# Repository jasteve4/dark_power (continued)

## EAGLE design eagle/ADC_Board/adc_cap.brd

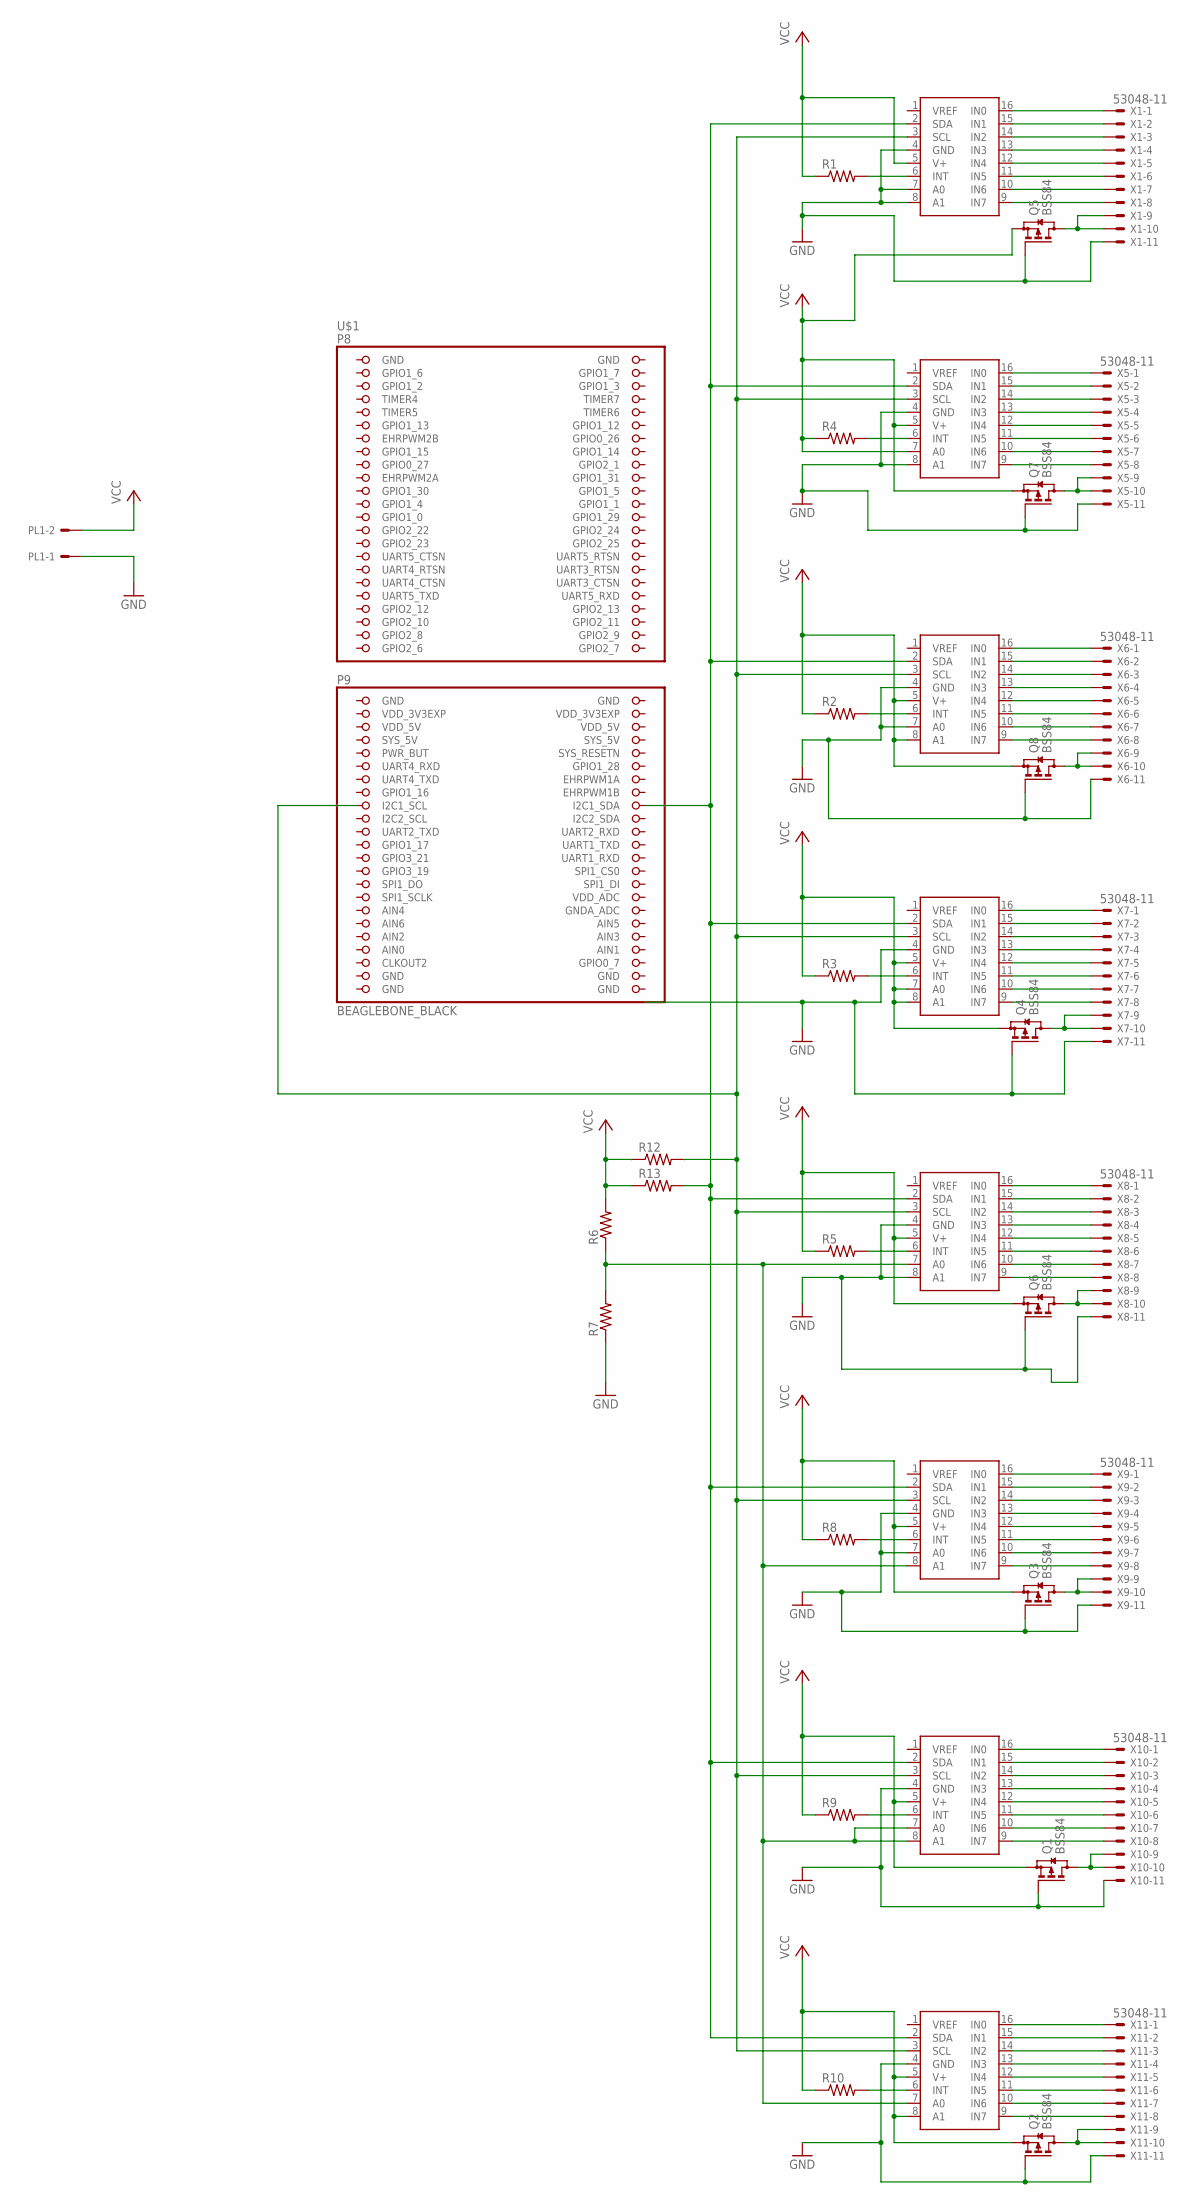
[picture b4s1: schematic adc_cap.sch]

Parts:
PL1: 555X-2H; 5569-2
Q1, Q2, Q3, Q4, Q5, Q6, Q7, Q8: BSS84; SOT23
R1, R2, R3, R4, R5, R6, R7, R8, R9, R10, R12, R13: R-US_R0805; R0805
U$1: BEAGLEBONE_BLACK; BEAGEBONE
U$2, U$3, U$4, U$5, U$6, U$7, U$8, U$9: ADC128D818; ADC12_SD
X1, X5, X6, X7, X8, X9, X10, X11: 53048-11

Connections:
AIN0: U$1.146 (AIN0)
GND: PL1.1, Q1.1 (G), Q2.1 (G), Q3.1 (G), Q4.1 (G), Q5.1 (G), Q6.1 (G), Q7.1 (G), Q8.1 (G), R7.1, U$1.137 (GND), U$1.138 (GND), U$1.139 (GND), U$1.140 (GND), U$1.141 (GND), U$1.142 (GND), U$1.183 (GND), U$1.184 (GND), U$2.4 (GND), U$2.8 (A1), U$3.4 (GND), U$3.7 (A0), U$3.8 (A1), U$4.4 (GND), U$4.7 (A0), U$5.4 (GND), U$6.4 (GND), U$6.8 (A1), U$7.4 (GND), U$7.7 (A0), U$8.4 (GND), U$9.4 (GND), X1.11, X5.11, X6.11, X7.11, X8.11, X9.11, X10.11, X11.11
unnamed: U$3.16 (IN0), X1.1
unnamed: U$3.15 (IN1), X1.2
unnamed: U$3.14 (IN2), X1.3
unnamed: U$3.13 (IN3), X1.4
unnamed: U$3.12 (IN4), X1.5
unnamed: U$3.11 (IN5), X1.6
unnamed: U$3.10 (IN6), X1.7
unnamed: U$3.9 (IN7), X1.8
unnamed: U$9.16 (IN0), X11.1
unnamed: U$9.15 (IN1), X11.2
unnamed: U$9.14 (IN2), X11.3
unnamed: U$9.13 (IN3), X11.4
unnamed: U$9.12 (IN4), X11.5
unnamed: U$9.11 (IN5), X11.6
unnamed: U$9.10 (IN6), X11.7
unnamed: U$9.9 (IN7), X11.8
unnamed: U$8.16 (IN0), X10.1
unnamed: U$8.15 (IN1), X10.2
unnamed: R4.2, U$2.6 (INT)
unnamed: U$8.14 (IN2), X10.3
unnamed: U$8.13 (IN3), X10.4
unnamed: U$8.12 (IN4), X10.5
unnamed: U$8.11 (IN5), X10.6
unnamed: U$8.10 (IN6), X10.7
unnamed: U$8.9 (IN7), X10.8
unnamed: R2.2, U$4.6 (INT)
unnamed: U$7.16 (IN0), X9.1
unnamed: U$7.15 (IN1), X9.2
unnamed: U$7.14 (IN2), X9.3
unnamed: U$7.13 (IN3), X9.4
unnamed: U$7.12 (IN4), X9.5
unnamed: U$7.11 (IN5), X9.6
unnamed: U$7.10 (IN6), X9.7
unnamed: U$7.9 (IN7), X9.8
unnamed: R3.2, U$5.6 (INT)
unnamed: U$6.16 (IN0), X8.1
unnamed: U$6.15 (IN1), X8.2
unnamed: U$6.14 (IN2), X8.3
unnamed: U$6.13 (IN3), X8.4
unnamed: U$6.12 (IN4), X8.5
unnamed: U$6.11 (IN5), X8.6
unnamed: U$6.10 (IN6), X8.7
unnamed: U$6.9 (IN7), X8.8
unnamed: R5.2, U$6.6 (INT)
unnamed: R6.1, R7.2, U$6.7 (A0), U$7.8 (A1), U$8.7 (A0), U$8.8 (A1), U$9.7 (A0)
unnamed: U$5.16 (IN0), X7.1
unnamed: U$5.15 (IN1), X7.2
unnamed: U$5.14 (IN2), X7.3
unnamed: U$5.13 (IN3), X7.4
unnamed: U$5.12 (IN4), X7.5
unnamed: U$5.11 (IN5), X7.6
unnamed: U$5.10 (IN6), X7.7
unnamed: U$5.9 (IN7), X7.8
unnamed: R8.2, U$7.6 (INT)
unnamed: R12.2, U$1.168 (I2C1_SCL), U$2.3 (SCL), U$3.3 (SCL), U$4.3 (SCL), U$5.3 (SCL), U$6.3 (SCL), U$7.3 (SCL), U$8.3 (SCL), U$9.3 (SCL)
unnamed: U$4.16 (IN0), X6.1
unnamed: U$4.15 (IN1), X6.2
unnamed: U$4.14 (IN2), X6.3
unnamed: U$4.13 (IN3), X6.4
unnamed: U$4.12 (IN4), X6.5
unnamed: U$4.11 (IN5), X6.6
unnamed: U$4.10 (IN6), X6.7
unnamed: U$4.9 (IN7), X6.8
unnamed: R9.2, U$8.6 (INT)
unnamed: U$2.16 (IN0), X5.1
unnamed: U$2.15 (IN1), X5.2
unnamed: R1.2, U$3.6 (INT)
unnamed: U$2.14 (IN2), X5.3
unnamed: U$2.13 (IN3), X5.4
unnamed: U$2.12 (IN4), X5.5
unnamed: U$2.11 (IN5), X5.6
unnamed: U$2.10 (IN6), X5.7
unnamed: U$2.9 (IN7), X5.8
unnamed: R10.2, U$9.6 (INT)
unnamed: Q5.3 (D), X1.9, X1.10
unnamed: Q4.3 (D), X7.9, X7.10
unnamed: Q8.3 (D), X6.9, X6.10
unnamed: Q1.3 (D), X10.9, X10.10
unnamed: Q7.3 (D), X5.9, X5.10
unnamed: Q6.3 (D), X8.9, X8.10
unnamed: Q2.3 (D), X11.9, X11.10
unnamed: R13.2, U$1.165 (I2C1_SDA), U$2.2 (SDA), U$3.2 (SDA), U$4.2 (SDA), U$5.2 (SDA), U$6.2 (SDA), U$7.2 (SDA), U$8.2 (SDA), U$9.2 (SDA)
unnamed: Q3.3 (D), X9.9, X9.10
SYS_5V: U$1.178 (SYS_5V)
VCC: PL1.2, Q1.2 (S), Q2.2 (S), Q3.2 (S), Q4.2 (S), Q5.2 (S), Q6.2 (S), Q7.2 (S), Q8.2 (S), R1.1, R2.1, R3.1, R4.1, R5.1, R6.2, R8.1, R9.1, R10.1, R12.1, R13.1, U$2.5 (V+), U$2.7 (A0), U$3.5 (V+), U$4.5 (V+), U$4.8 (A1), U$5.5 (V+), U$5.7 (A0), U$5.8 (A1), U$6.5 (V+), U$7.5 (V+), U$8.5 (V+), U$9.5 (V+), U$9.8 (A1)
VDD_3V3EXP: U$1.181 (VDD_3V3EXP), U$1.182 (VDD_3V3EXP)
VDD_5V: U$1.179 (VDD_5V), U$1.180 (VDD_5V)

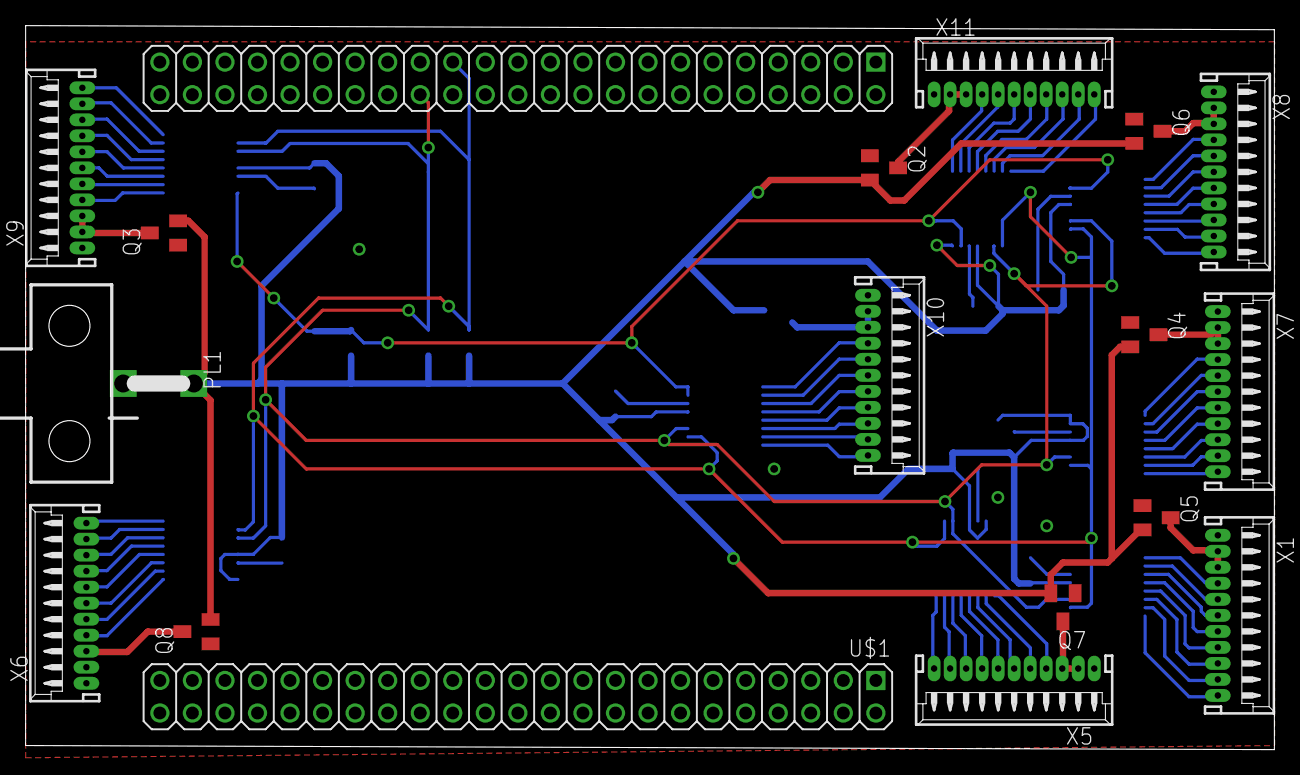
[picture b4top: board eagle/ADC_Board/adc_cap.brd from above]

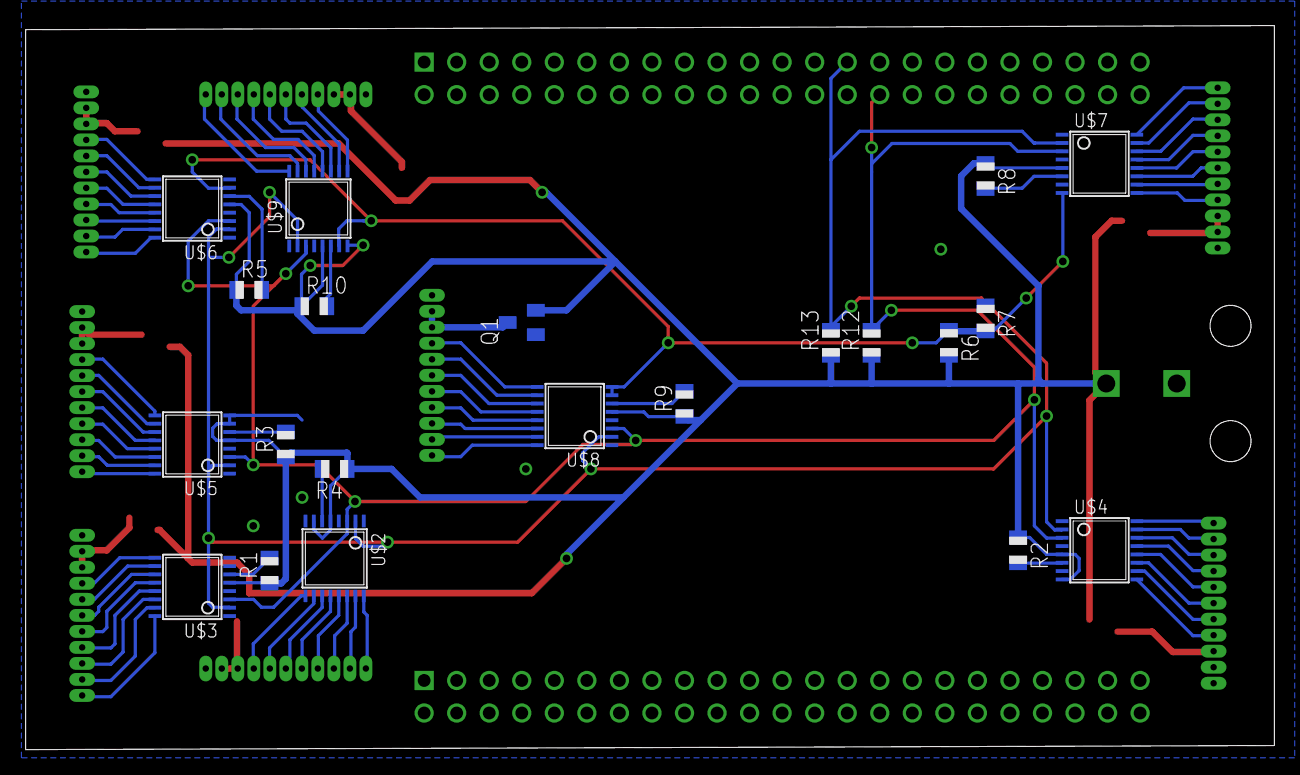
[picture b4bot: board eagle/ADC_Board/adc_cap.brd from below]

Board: 2 copper layers, 97.5 x 56.5 mm, 38 parts (21 on the bottom side), 87 nets.

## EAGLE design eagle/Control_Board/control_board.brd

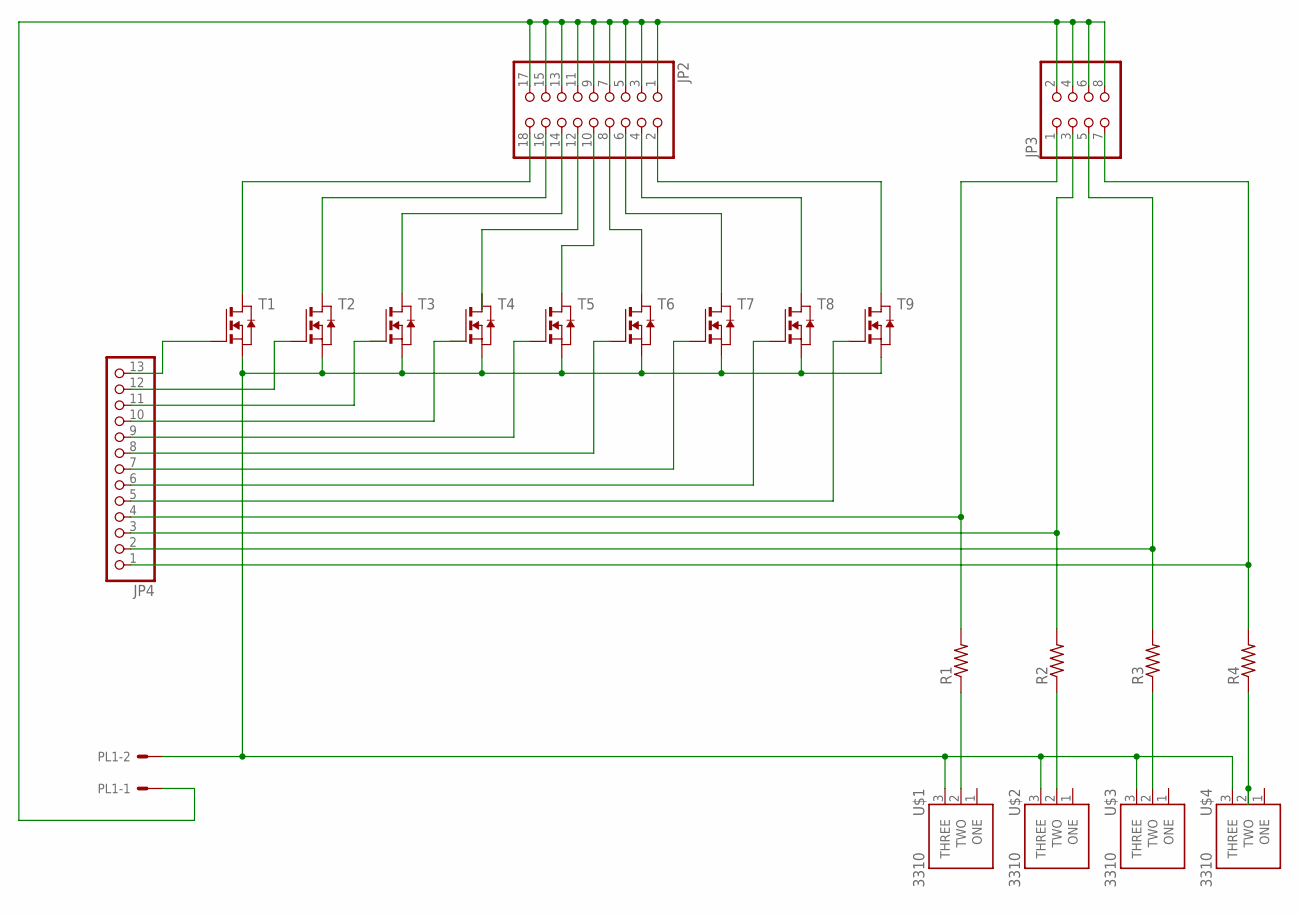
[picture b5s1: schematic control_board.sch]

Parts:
JP2: PINHD-2X9-BIG; 2X09-BIG
JP3: PINHD-2X4; 2X04
JP4: PINHD-1X13; 1X13
PL1: 555X-2H; 5569-2
R1, R2, R3, R4: R-US_R0805; R0805
T1, T2, T3, T4, T5, T6, T7, T8, T9: NMOSSOT223; SOT223
U$1, U$2, U$3, U$4: 3310-001; 3310-001-TH

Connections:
unnamed: JP4.13, T1.1 (G)
unnamed: JP4.12, T2.1 (G)
unnamed: JP4.9, T5.1 (G)
unnamed: PL1.2, T1.3 (S), T2.3 (S), T3.3 (S), T4.3 (S), T5.3 (S), T6.3 (S), T7.3 (S), T8.3 (S), T9.3 (S), U$1.3 (THREE), U$2.3 (THREE), U$3.3 (THREE), U$4.3 (THREE)
unnamed: JP3.3, JP4.3, R2.2
unnamed: R3.1, U$3.2 (TWO)
unnamed: JP3.5, JP4.2, R3.2
unnamed: R4.1, U$4.2 (TWO)
unnamed: R1.1, U$1.2 (TWO)
unnamed: JP3.1, JP4.4, R1.2
unnamed: R2.1, U$2.2 (TWO)
unnamed: JP3.7, JP4.1, R4.2
unnamed: JP2.18, T1.2 (D), T1.4 (D)
unnamed: JP2.16, T2.2 (D), T2.4 (D)
unnamed: JP2.2, T9.2 (D), T9.4 (D)
unnamed: JP2.4, T8.2 (D), T8.4 (D)
unnamed: JP2.6, T7.2 (D), T7.4 (D)
unnamed: JP2.8, T6.2 (D), T6.4 (D)
unnamed: JP2.14, T3.2 (D), T3.4 (D)
unnamed: JP2.10, T5.2 (D), T5.4 (D)
unnamed: JP2.1, JP2.3, JP2.5, JP2.7, JP2.9, JP2.11, JP2.13, JP2.15, JP2.17, JP3.2, JP3.4, JP3.6, JP3.8, PL1.1
unnamed: JP4.8, T6.1 (G)
unnamed: JP4.7, T7.1 (G)
unnamed: JP4.6, T8.1 (G)
unnamed: JP4.5, T9.1 (G)

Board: 2 copper layers, 21 parts (0 on the bottom side), 25 nets, no tracks yet.

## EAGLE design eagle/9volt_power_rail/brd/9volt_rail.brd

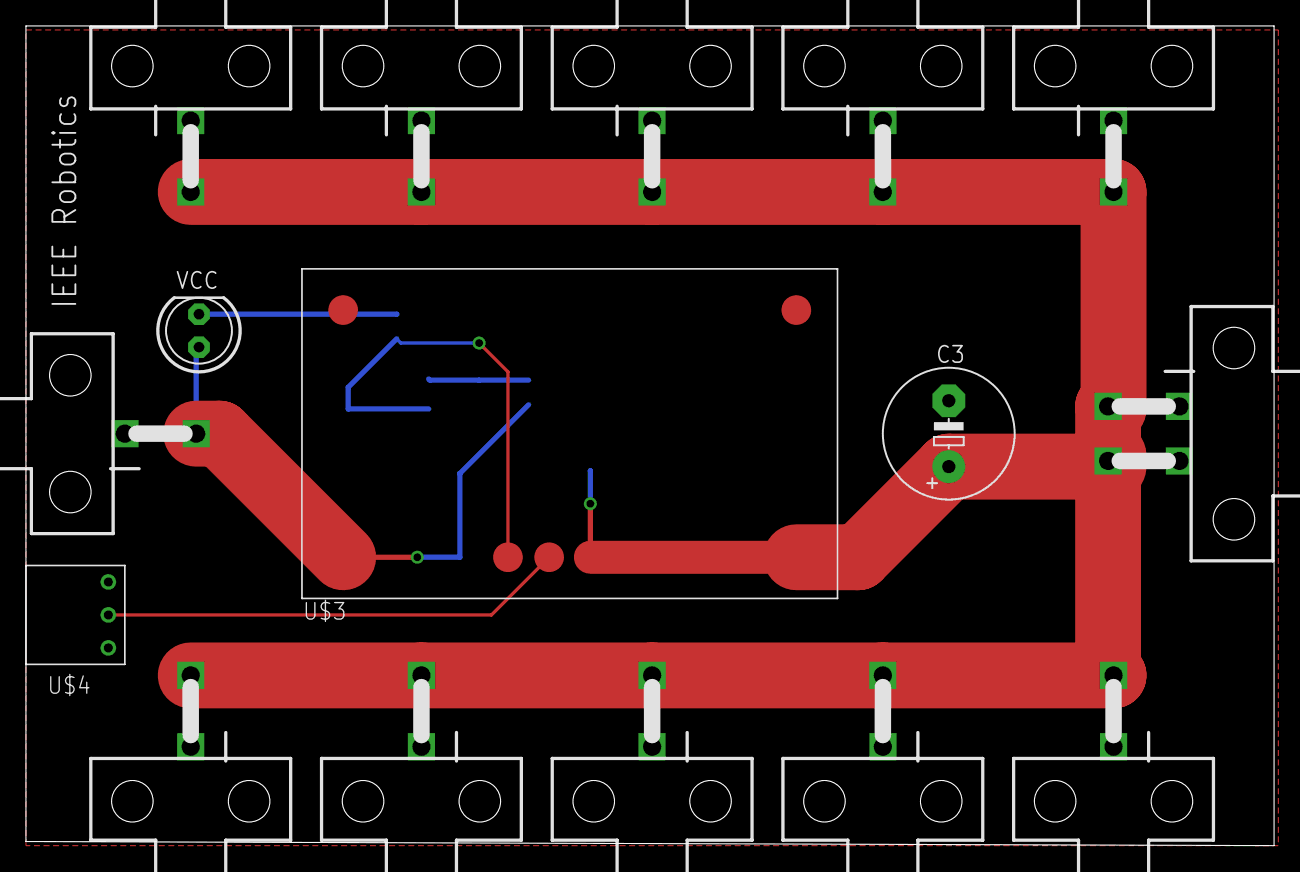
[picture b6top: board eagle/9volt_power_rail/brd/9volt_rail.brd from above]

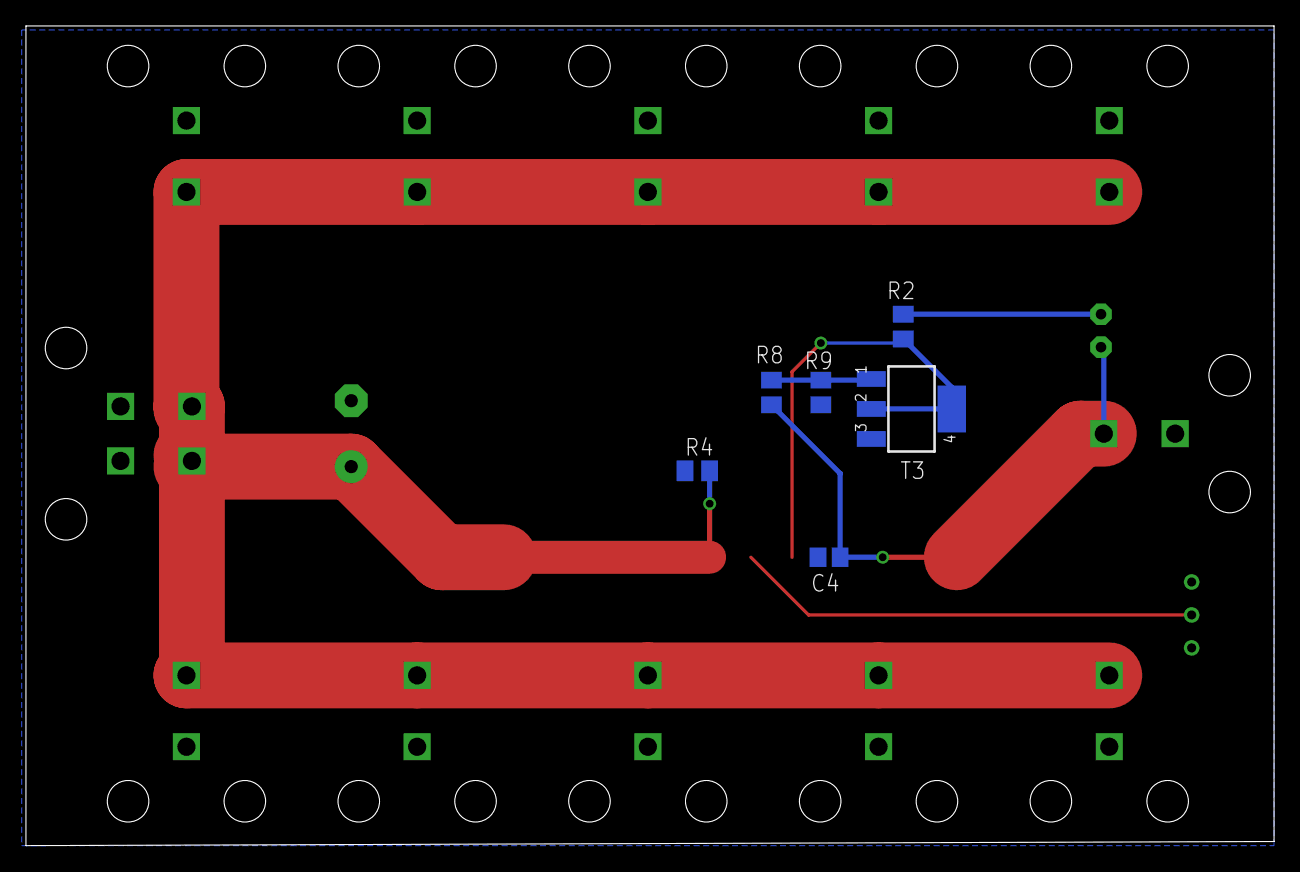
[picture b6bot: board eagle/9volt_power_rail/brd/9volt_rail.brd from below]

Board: 2 copper layers, 96.2 x 63.2 mm, 22 parts (6 on the bottom side), 7 nets.

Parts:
C3: 330uF; E5-10,5
C4: 2.2uF; C0805
PL1, PL2, PL3, PL4, PL5, PL6, PL7, PL8, PL9, PL10, PL12: 5569-2
PL11: 5569-4
R2, R4, R8, R9: M0805
T3: SOT223
U$3: PTH78020-SMD; PTN78020-SND
U$4: 3310-001; 3310-001-TH
VCC: LED5MM

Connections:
GND: C3.-, C4.2, PL1.1, PL2.1, PL3.1, PL4.1, PL5.1, PL6.1, PL7.1, PL8.1, PL9.1, PL10.1, PL11.1, PL11.2, PL12.1, R4.2, R9.2, T3.3, U$3.1, U$3.7, U$4.3
unnamed: C3.+, PL1.2, PL2.2, PL3.2, PL4.2, PL5.2, PL6.2, PL7.2, PL8.2, PL9.2, PL10.2, PL11.3, PL11.4, R4.1, U$3.5, U$3.6
unnamed: R2.1, VCC.K
unnamed: R2.2, T3.2, T3.4, U$3.3
unnamed: U$3.4, U$4.2
unnamed: R8.2, R9.1, T3.1
VCC: C4.1, PL12.2, R8.1, U$3.2, VCC.A

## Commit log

2014-08-06 created PTH78020 part
2014-08-12 moving to lab computer
2014-08-13 working on width errors
2014-08-13 cleaning up
2014-08-14 Update to Control board
2014-08-14 Cleanning up
2014-08-14 Moving files to home file
2014-08-14 Done with clean up
2014-08-16 cleaning up extra dir
2014-08-25 Done with revision B
2014-08-28 Update to dark power and update to ADC cape
2014-09-05 Done with power board and adc cape
2014-09-09 adc rev all most done
2014-10-02 update to adc cape
2015-01-11 update to the courrent files
